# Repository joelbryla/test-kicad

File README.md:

## Recommended Addons:

- impartGUI

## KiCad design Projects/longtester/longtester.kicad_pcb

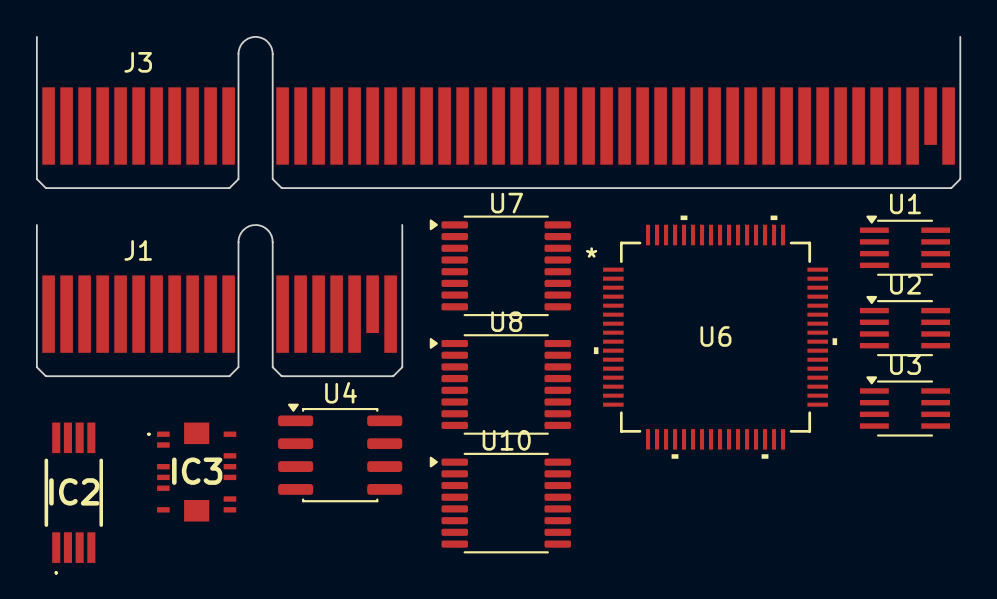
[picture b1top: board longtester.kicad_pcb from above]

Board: 2 copper layers, 51.3 x 18.8 mm, 12 parts (0 on the bottom side), 21 nets, no tracks yet.

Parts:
IC2: CT456-H00B5-TS08; CT456H00B5TS08
IC3: INA750BIREMR; INA740BIREMR
J1: Bus_PCI_Express_x1; BUS_PCIexpress_x1
J3: Bus_PCI_Express_x8; BUS_PCIexpress_x8
U1, U2, U3: 74AHC2G00; SSOP-8_2.95x2.8mm_P0.65mm
U4: LT1461AxS8-2.5; SOIC-8_3.9x4.9mm_P1.27mm
U6: AD7606C-16BSTZ; ST-64-2_ADI-L
U7: ULN2003; TSSOP-16_4.4x5mm_P0.65mm
U8, U10: 74HCT238; TSSOP-16_4.4x5mm_P0.65mm

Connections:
+3V3: IC2.2 (VCC), IC3.3 (VS), J1.B10 (3.3Vaux), U1.8 (VCC), U2.8 (VCC), U3.8 (VCC), U6.3 (OS_0), U6.4 (OS_1), U6.5 (OS_2), U6.7 (*STBY), U6.8 (RANGE), U6.23 (VDRIVE), U6.34 (REF_SELECT), U7.9 (COM), U8.6 (E3), U8.16 (VCC), U10.6 (E3), U10.16 (VCC)
+5V: U6.1 (AVCC), U6.37 (AVCC), U6.38 (AVCC), U6.48 (AVCC)
/VBAT1_EN.BAT1A: U7.4 (I4), U8.11 (Y4)
/VBAT1_EN.BAT1B: U7.5 (I5), U8.10 (Y5)
/VBAT1_EN.EXT1: U3.7, U7.2 (I2)
/VBAT1_EN.EXT2: U2.6, U7.3 (I3), U8.12 (Y3)
/VBAT1_EN.SHORT: U7.1 (I1), U8.14 (Y1)
/VBAT1_EN_EXT1_REQUEST: U1.1, U1.2, U8.13 (Y2)
/VBAT2_EN_EXT2_REQUEST: U2.1, U2.2, U10.13 (Y2)
GND: IC2.7 (GND), IC2.8 (TEST), IC3.5 (GND), IC3.12 (REF), J1.A4 (GND), J1.A12 (GND), J1.A15 (GND), J1.A18 (GND), J1.B4 (GND), J1.B7 (GND), J1.B13 (GND), J1.B16 (GND), J1.B18 (GND), U1.4 (GND), U2.4 (GND), U3.4 (GND), U7.8 (GND), U8.4 (~E1), U8.5 (~E2), U8.8 (GND), U10.4 (~E1), U10.5 (~E2), U10.8 (GND)
GNDA: U6.2 (AGND), U6.26 (AGND), U6.35 (AGND), U6.40 (AGND), U6.41 (AGND), U6.43 (REFGND), U6.46 (REFGND), U6.47 (AGND), U6.50 (V1-), U6.52 (V2-), U6.54 (V3-), U6.56 (V4-), U6.58 (V5-), U6.60 (V6-), U6.62 (V7-), U6.64 (V8-)
unnamed: J1.A9 (+3.3V), J1.A10 (+3.3V), J1.B8 (+3.3V)
unnamed: J1.A2 (+12V), J1.A3 (+12V), J1.B1 (+12V), J1.B2 (+12V), J1.B3 (+12V)
unnamed: J3.A9 (+3.3V), J3.A10 (+3.3V), J3.B8 (+3.3V)
unnamed: J3.A2 (+12V), J3.A3 (+12V), J3.B1 (+12V), J3.B2 (+12V), J3.B3 (+12V)
unnamed: J3.A4 (GND), J3.A12 (GND), J3.A15 (GND), J3.A18 (GND), J3.A20 (GND), J3.A23 (GND), J3.A24 (GND), J3.A27 (GND), J3.A28 (GND), J3.A31 (GND), J3.A34 (GND), J3.A37 (GND), J3.A38 (GND), J3.A41 (GND), J3.A42 (GND), J3.A45 (GND), J3.A46 (GND), J3.A49 (GND), J3.B4 (GND), J3.B7 (GND), J3.B13 (GND), J3.B16 (GND), J3.B18 (GND), J3.B21 (GND), J3.B22 (GND), J3.B25 (GND), J3.B26 (GND), J3.B29 (GND), J3.B32 (GND), J3.B35 (GND), J3.B36 (GND), J3.B39 (GND), J3.B40 (GND), J3.B43 (GND), J3.B44 (GND), J3.B47 (GND), J3.B49 (GND)
unnamed: U1.3, U3.1, U3.2
unnamed: U1.5, U1.7
unnamed: U2.3, U3.5, U3.6
unnamed: U2.5, U2.7
unnamed: U6.44 (REFCAPA), U6.45 (REFCAPB)

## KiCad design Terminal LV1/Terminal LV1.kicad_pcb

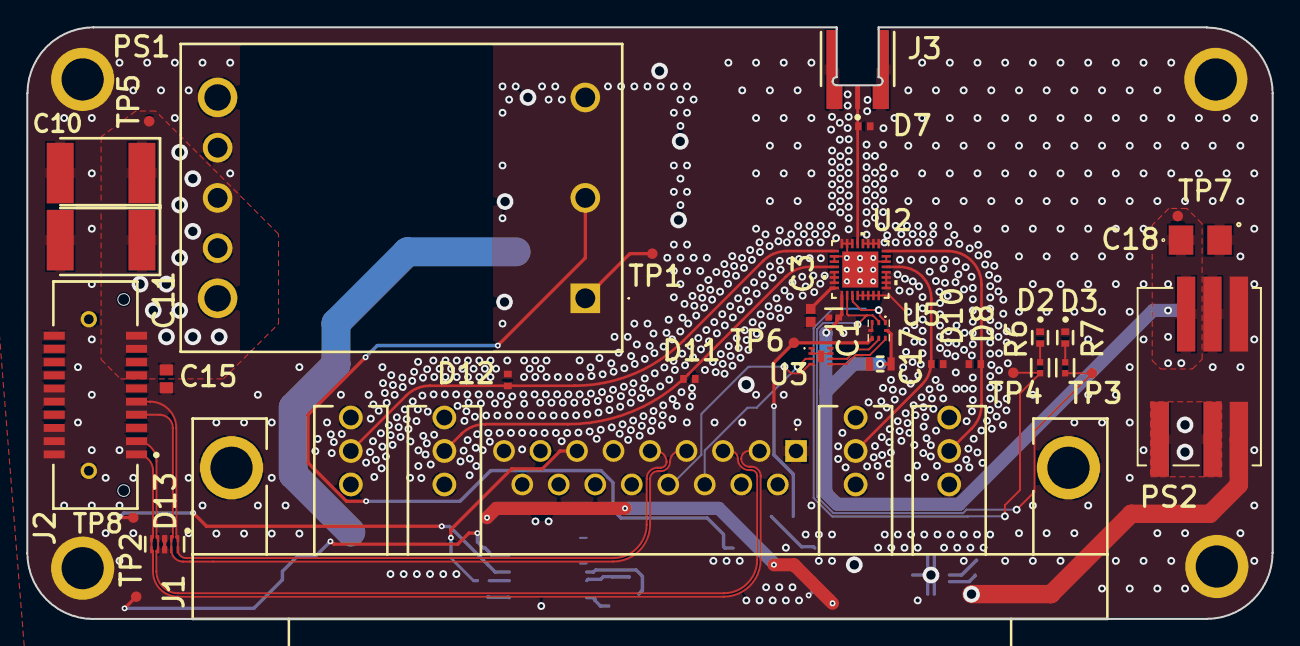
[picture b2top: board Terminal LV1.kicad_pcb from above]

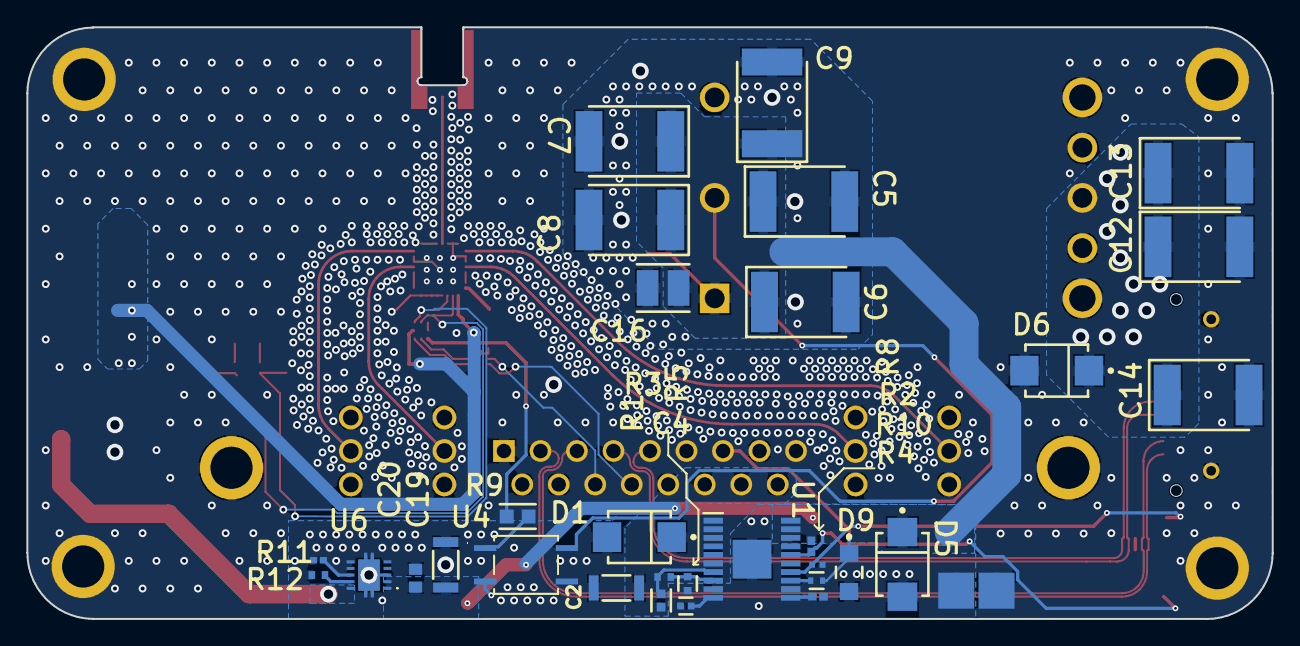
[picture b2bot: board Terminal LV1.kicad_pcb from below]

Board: 4 copper layers, 94.5 x 44.9 mm, 63 parts (30 on the bottom side), 38 nets.

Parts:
C1: GRM155R71H103KA88J; FP-GRM155-0_05-IPC_C
C2, C19: 1uF 100V; FP-CGA5L-0_3-0_1-IPC_B
C3: GRM155R71H102KA01D; CAPC1005X55X25ML5T10
C4: 15nF; FP-C0402-BB-MFG
C5, C6, C7, C8, C9, C10, C11, C12, C13, C14: 47u; CAPPC7343X430N
C15, C20: 0.1u; CAPC1608X92X38NL15T08
C16: 10uF 50V; FP-1210-L_3_2_0_5-W_2_5_0-IPC_C
C17: 1u; FP-CGA3E-0_3-0_1-IPC_C
C18: 47u; T520B
D1, D5, D6: SMBJ36A; FP-SMBJ-MFG
D2, D3: STAT2; FP-SML-P1-MFG
D7, D8, D10, D11, D12: 0402ESDA-AEC1; 0402ESDAAEC1
D9: SMF24A; FP-SMF24A-MFG
D13: TPD4E02B04QDQARQ1; FP-TPD4E02B04QDQARQ1-MFG
J1: 685M21WA4SL461
J2: T1M-10-GF-DV; FP-T1M-10-GF-DV-MFG
J3: 73300-0020; New footprint 1
PS1: CHS1202424-B; CHS1202424B
PS2: TDN 1-2410WISM; TDN 1WISM SINGLE_TRP
R1: 274k; FP-CRCW0402-e3-IPC_A
R2: 16.5K; RESC1005X40X25LL05T05
R3, R12: 47k; WRIS-RSKS_0402
R4: 2.7K; RESC1005X40X25NL10T10
R5: 10K; FP-RG1005-MFG
R6, R7: 1K; FP-RK73H1E-IPC_C
R8: 20K; RESC1005X40X25NL10T10
R9: MCT0603MD4700DP500; FP-MCT0603-IPC_A
R10: 10K 0.2W; FP-ESR01-MFG
R11: 33K; RESC1005X40X25LL10T10
TP1, TP2, TP3, TP4, TP5, TP6, TP7, TP8: testpoint1; testpoint1-Footprint-1
U1: TPS16630PWPT; SOP65P640X120-21N
U2: TS8441L; QFN32_4X4X0p8_TGT
U3: NUF4403MNT1G; ONSC-DFN-8-506AK-01_V
U4: VOM617A-4X001T; SMD-4_VOM617A_VIS
U5: PCA9570GMH
U6: TPS16412DRCR

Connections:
3V3: C1.2, C17.1, C18.1, PS2.7, TP7.1, U2.1, U5.8
ANT1: D8.1, J1.A12, U2.16
ANT2: D10.1, J1.A22, U2.13
ANT3: D11.1, J1.A32, U2.28
ANT4: D12.1, J1.A42, U2.25
DEPLOYMENT: R10.2, U1.13
DEPLOYMENT_C: D9.1, J1.7, R10.1
GND: C1.1, C3.2, C10.2, C11.2, C12.2, C13.2, C14.2, C15.1, C17.2, C18.2, D2.1, D3.1, D6.2, D7.2, D8.2, D10.2, D11.2, D12.2, D13.3, D13.8, J1.1, J1.8, J1.10, J1.11, J1.14, J1.15, J1.16, J1.18, J1.19, J1.A11, J1.A13, J1.A21, J1.A23, J1.A31, J1.A33, J1.A41, J1.A43, J2.5, J2.8, J2.11, J2.14, J2.16, J2.18, J2.20, J2.21, J2.22, J3.2, PS1.4, PS1.5, PS2.6, U2.4, U2.5, U2.6, U2.7, U2.8, U2.9, U2.10, U2.11, U2.12, U2.14, U2.15, U2.17, U2.18, U2.19, U2.20, U2.22, U2.23, U2.24, U2.26, U2.27, U2.29, U2.30, U2.31, U2.33, U3.1, U3.2, U3.7, U3.8, U3.9, U4.2, U5.3, U5.4
ISOGND: C2.2, C4.2, C5.2, C6.2, C7.2, C8.2, C9.2, C16.2, C19.2, C20.1, D1.2, D5.2, D9.2, J1.9, PS1.3, PS2.2, PS2.4, R2.1, R4.1, R5.1, R11.1, R12.1, U1.9, U1.12, U1.21, U4.3, U6.3, U6.6, U6.11, U6.12, U6.13, U6.14, U6.15
MOD_RF: D7.1, J3.1, U2.21
NetC3_1: C3.1, U2.32
NetC4_1: C4.1, U1.10
NetD2_2: D2.2, R6.1
NetD3_2: D3.2, R7.1
NetPS1_2: PS1.2, U4.4
NetR1_2: R1.2, R3.2, U1.7
NetR2_2: R2.2, TP8.1, U1.14
NetR3_1: R3.1, R5.2, U1.8
NetR4_2: R4.2, U1.11
NetR9_2: R9.2, U4.1
NetR11_2: R11.2, U6.8
NetR12_2: R12.2, U6.9
PGOOD: R8.1, TP2.1, U1.16
PSU_EN: R9.1, TP6.1, U5.5
RF_SEL0: R7.2, TP3.1, U2.2, U5.2
RF_SEL1: R6.2, TP4.1, U2.3, U5.1
RX_N: D13.5, D13.6, J1.2, J2.1
RX_P: D13.4, D13.7, J1.3, J2.3
SCL: U3.6, U5.6
SCL_C: J1.12, U3.3
SDA: U3.5, U5.7
SDA_C: J1.13, U3.4
TX_N: D13.2, D13.9, J1.4, J2.7
TX_P: D13.1, D13.10, J1.5, J2.9
VEXT: C5.1, C6.1, C7.1, C8.1, C9.1, C16.1, C19.1, C20.2, D5.1, PS1.1, R8.2, TP1.1, U1.18, U1.19, U1.20, U6.1, U6.2
VEXT_3V3: PS2.1, U6.10
VEXT_C: C2.1, D1.1, J1.17, R1.1, U1.1, U1.2, U1.3, U1.6
VMODEM: C10.1, C11.1, C12.1, C13.1, C14.1, C15.2, D6.1, J2.13, J2.15, PS1.7, PS1.8, TP5.1
